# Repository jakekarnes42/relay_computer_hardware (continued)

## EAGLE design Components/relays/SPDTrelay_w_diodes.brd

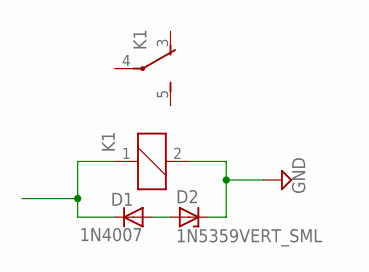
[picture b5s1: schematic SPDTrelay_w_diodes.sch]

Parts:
D1: 1N4007; RAD2,5
D2: 1N5359VERT_SML; RAD2.5_D2
K1: HF41F-12-Z

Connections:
D$1: D1.A, D2.A
GND: D2.C, K1.2
IN: D1.C, K1.1

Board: 2 copper layers, 3 parts (0 on the bottom side), 3 nets, no tracks yet.

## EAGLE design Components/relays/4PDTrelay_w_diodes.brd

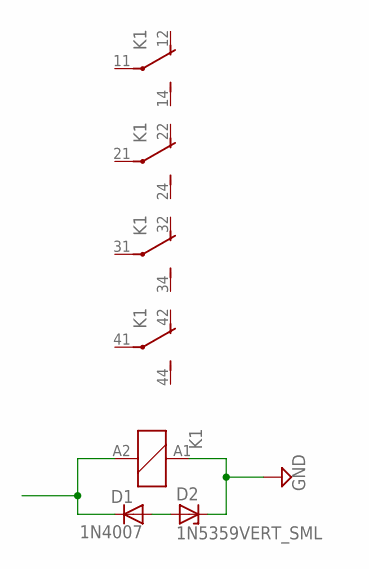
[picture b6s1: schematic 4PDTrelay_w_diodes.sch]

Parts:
D1: 1N4007; RAD2,5
D2: 1N5359VERT_SML; RAD2.5_D2
K1: PY14-02

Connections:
D$1: D1.A, D2.A
GND: D2.C, K1.A1 (1)
IN: D1.C, K1.A2 (2)

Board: 2 copper layers, 3 parts (0 on the bottom side), 3 nets, no tracks yet.

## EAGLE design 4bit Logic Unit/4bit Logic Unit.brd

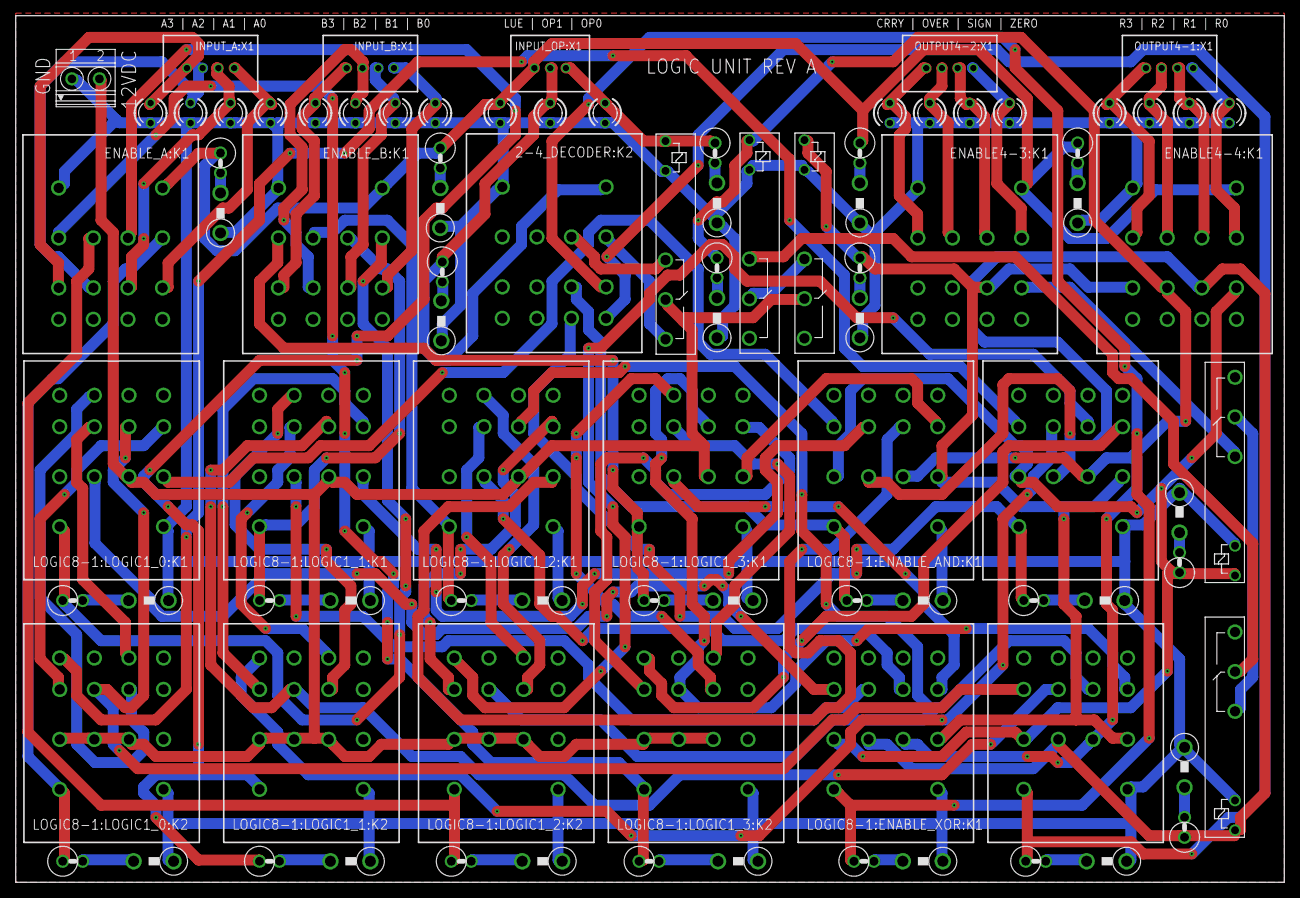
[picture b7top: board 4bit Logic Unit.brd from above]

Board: 2 copper layers, 161.3 x 110.2 mm, 91 parts (0 on the bottom side), 93 nets.

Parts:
2-4_DECODER:D1, 2-4_DECODER:D3: 1N4007; RAD2,5
2-4_DECODER:D2, 2-4_DECODER:D4: 1N5359; C1702-05
2-4_DECODER:K1: HF41F-12-Z
2-4_DECODER:K2: PY14-02
ENABLE4-3:D1, ENABLE4-4:D1: 1N4007; RAD2,5
ENABLE4-3:D2, ENABLE4-4:D2: 1N5359; C1702-05
ENABLE4-3:K1, ENABLE4-4:K1: PY14-02
ENABLE_A:D1: 1N4007; RAD2,5
ENABLE_A:D2: 1N5359; C1702-05
ENABLE_A:K1: PY14-02
ENABLE_B:D1: 1N4007; RAD2,5
ENABLE_B:D2: 1N5359; C1702-05
ENABLE_B:K1: PY14-02
INPUT_A:LED0, INPUT_A:LED1, INPUT_A:LED2, INPUT_A:LED3: LED3MM
INPUT_A:X1: 55932-0430
INPUT_B:LED0, INPUT_B:LED1, INPUT_B:LED2, INPUT_B:LED3: LED3MM
INPUT_B:X1: 55932-0430
INPUT_OP:LED0, INPUT_OP:LED1, INPUT_OP:LED2: LED3MM
INPUT_OP:X1: 55932-0330
LOGIC8-1:ENABLE_AND:D1, LOGIC8-1:ENABLE_NOT:D1, LOGIC8-1:ENABLE_OR:D1, LOGIC8-1:ENABLE_XOR:D1, LOGIC8-1:LOGIC1_0:D1, LOGIC8-1:LOGIC1_0:D3, LOGIC8-1:LOGIC1_1:D1, LOGIC8-1:LOGIC1_1:D3, LOGIC8-1:LOGIC1_2:D1, LOGIC8-1:LOGIC1_2:D3, LOGIC8-1:LOGIC1_3:D1, LOGIC8-1:LOGIC1_3:D3: 1N4007; RAD2,5
LOGIC8-1:ENABLE_AND:D2, LOGIC8-1:ENABLE_NOT:D2, LOGIC8-1:ENABLE_OR:D2, LOGIC8-1:ENABLE_XOR:D2, LOGIC8-1:LOGIC1_0:D2, LOGIC8-1:LOGIC1_0:D4, LOGIC8-1:LOGIC1_1:D2, LOGIC8-1:LOGIC1_1:D4, LOGIC8-1:LOGIC1_2:D2, LOGIC8-1:LOGIC1_2:D4, LOGIC8-1:LOGIC1_3:D2, LOGIC8-1:LOGIC1_3:D4: 1N5359; C1702-05
LOGIC8-1:ENABLE_AND:K1, LOGIC8-1:ENABLE_NOT:K1, LOGIC8-1:ENABLE_OR:K1, LOGIC8-1:ENABLE_XOR:K1, LOGIC8-1:LOGIC1_0:K1, LOGIC8-1:LOGIC1_0:K2, LOGIC8-1:LOGIC1_1:K1, LOGIC8-1:LOGIC1_1:K2, LOGIC8-1:LOGIC1_2:K1, LOGIC8-1:LOGIC1_2:K2, LOGIC8-1:LOGIC1_3:K1, LOGIC8-1:LOGIC1_3:K2: PY14-02
OUTPUT4-1:LED0, OUTPUT4-1:LED1, OUTPUT4-1:LED2, OUTPUT4-1:LED3, OUTPUT4-2:LED0, OUTPUT4-2:LED1, OUTPUT4-2:LED2, OUTPUT4-2:LED3: LED3MM
OUTPUT4-1:X1, OUTPUT4-2:X1: 55932-0430
PWR_BLK:PWR: PWR_BLK; 1751248
ZERO_DETECT1:D1, ZERO_DETECT1:D3, ZERO_DETECT1:D5, ZERO_DETECT1:D7: 1N4007; RAD2,5
ZERO_DETECT1:D2, ZERO_DETECT1:D4, ZERO_DETECT1:D6, ZERO_DETECT1:D8: 1N5359; C1702-05
ZERO_DETECT1:K1, ZERO_DETECT1:K2, ZERO_DETECT1:K3, ZERO_DETECT1:K4: HF41F-12-Z

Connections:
2-4_DECODER:D$1: 2-4_DECODER:D1.A, 2-4_DECODER:D2.A
2-4_DECODER:D$2: 2-4_DECODER:D3.A, 2-4_DECODER:D4.A
2-4_DECODER:N$1: 2-4_DECODER:K1.5, 2-4_DECODER:K2.41
2-4_DECODER:N$2: 2-4_DECODER:K1.3, 2-4_DECODER:K2.31
+12V: 2-4_DECODER:K1.4, LOGIC8-1:LOGIC1_0:K1.21, LOGIC8-1:LOGIC1_0:K2.21, LOGIC8-1:LOGIC1_0:K2.31, LOGIC8-1:LOGIC1_0:K2.41, LOGIC8-1:LOGIC1_1:K1.21, LOGIC8-1:LOGIC1_1:K2.21, LOGIC8-1:LOGIC1_1:K2.31, LOGIC8-1:LOGIC1_1:K2.41, LOGIC8-1:LOGIC1_2:K1.21, LOGIC8-1:LOGIC1_2:K2.21, LOGIC8-1:LOGIC1_2:K2.31, LOGIC8-1:LOGIC1_2:K2.41, LOGIC8-1:LOGIC1_3:K1.21, LOGIC8-1:LOGIC1_3:K2.21, LOGIC8-1:LOGIC1_3:K2.31, LOGIC8-1:LOGIC1_3:K2.41, PWR_BLK:PWR.2, ZERO_DETECT1:K1.4
CARRY: ENABLE4-3:K1.11, OUTPUT4-2:LED3.A, OUTPUT4-2:X1.1
ENABLE4-3:D$1: ENABLE4-3:D1.A, ENABLE4-3:D2.A
ENABLE4-4:D$1: ENABLE4-4:D1.A, ENABLE4-4:D2.A
ENABLE_A:D$1: ENABLE_A:D1.A, ENABLE_A:D2.A
ENABLE_B:D$1: ENABLE_B:D1.A, ENABLE_B:D2.A
GND: 2-4_DECODER:D2.C, 2-4_DECODER:D4.C, 2-4_DECODER:K1.2, 2-4_DECODER:K2.A1, ENABLE4-3:D2.C, ENABLE4-3:K1.A1, ENABLE4-4:D2.C, ENABLE4-4:K1.A1, ENABLE_A:D2.C, ENABLE_A:K1.A1, ENABLE_B:D2.C, ENABLE_B:K1.A1, INPUT_A:LED0.K, INPUT_A:LED1.K, INPUT_A:LED2.K, INPUT_A:LED3.K, INPUT_B:LED0.K, INPUT_B:LED1.K, INPUT_B:LED2.K, INPUT_B:LED3.K, INPUT_OP:LED0.K, INPUT_OP:LED1.K, INPUT_OP:LED2.K, LOGIC8-1:ENABLE_AND:D2.C, LOGIC8-1:ENABLE_AND:K1.A1, LOGIC8-1:ENABLE_NOT:D2.C, LOGIC8-1:ENABLE_NOT:K1.A1, LOGIC8-1:ENABLE_OR:D2.C, LOGIC8-1:ENABLE_OR:K1.A1, LOGIC8-1:ENABLE_XOR:D2.C, LOGIC8-1:ENABLE_XOR:K1.A1, LOGIC8-1:LOGIC1_0:D2.C, LOGIC8-1:LOGIC1_0:D4.C, LOGIC8-1:LOGIC1_0:K1.A1, LOGIC8-1:LOGIC1_0:K2.A1, LOGIC8-1:LOGIC1_1:D2.C, LOGIC8-1:LOGIC1_1:D4.C, LOGIC8-1:LOGIC1_1:K1.A1, LOGIC8-1:LOGIC1_1:K2.A1, LOGIC8-1:LOGIC1_2:D2.C, LOGIC8-1:LOGIC1_2:D4.C, LOGIC8-1:LOGIC1_2:K1.A1, LOGIC8-1:LOGIC1_2:K2.A1, LOGIC8-1:LOGIC1_3:D2.C, LOGIC8-1:LOGIC1_3:D4.C, LOGIC8-1:LOGIC1_3:K1.A1, LOGIC8-1:LOGIC1_3:K2.A1, OUTPUT4-1:LED0.K, OUTPUT4-1:LED1.K, OUTPUT4-1:LED2.K, OUTPUT4-1:LED3.K, OUTPUT4-2:LED0.K, OUTPUT4-2:LED1.K, OUTPUT4-2:LED2.K, OUTPUT4-2:LED3.K, PWR_BLK:PWR.1, ZERO_DETECT1:D2.C, ZERO_DETECT1:D4.C, ZERO_DETECT1:D6.C, ZERO_DETECT1:D8.C, ZERO_DETECT1:K1.2, ZERO_DETECT1:K2.2, ZERO_DETECT1:K3.2, ZERO_DETECT1:K4.2
LOGIC8-1:AND0: LOGIC8-1:ENABLE_AND:K1.44, LOGIC8-1:LOGIC1_0:K1.11
LOGIC8-1:AND1: LOGIC8-1:ENABLE_AND:K1.34, LOGIC8-1:LOGIC1_1:K1.11
LOGIC8-1:AND2: LOGIC8-1:ENABLE_AND:K1.24, LOGIC8-1:LOGIC1_2:K1.11
LOGIC8-1:AND3: LOGIC8-1:ENABLE_AND:K1.14, LOGIC8-1:LOGIC1_3:K1.11
LOGIC8-1:ENABLE_AND:D$1: LOGIC8-1:ENABLE_AND:D1.A, LOGIC8-1:ENABLE_AND:D2.A
LOGIC8-1:ENABLE_NOT:D$1: LOGIC8-1:ENABLE_NOT:D1.A, LOGIC8-1:ENABLE_NOT:D2.A
LOGIC8-1:ENABLE_OR:D$1: LOGIC8-1:ENABLE_OR:D1.A, LOGIC8-1:ENABLE_OR:D2.A
LOGIC8-1:ENABLE_XOR:D$1: LOGIC8-1:ENABLE_XOR:D1.A, LOGIC8-1:ENABLE_XOR:D2.A
LOGIC8-1:LOGIC1_0:D$1: LOGIC8-1:LOGIC1_0:D1.A, LOGIC8-1:LOGIC1_0:D2.A
LOGIC8-1:LOGIC1_0:D$2: LOGIC8-1:LOGIC1_0:D3.A, LOGIC8-1:LOGIC1_0:D4.A
LOGIC8-1:LOGIC1_0:N$1: LOGIC8-1:LOGIC1_0:K1.14, LOGIC8-1:LOGIC1_0:K2.44
LOGIC8-1:LOGIC1_0:N$3: LOGIC8-1:LOGIC1_0:K1.32, LOGIC8-1:LOGIC1_0:K2.24
LOGIC8-1:LOGIC1_0:N$4: LOGIC8-1:LOGIC1_0:K1.34, LOGIC8-1:LOGIC1_0:K2.22
LOGIC8-1:LOGIC1_1:D$1: LOGIC8-1:LOGIC1_1:D1.A, LOGIC8-1:LOGIC1_1:D2.A
LOGIC8-1:LOGIC1_1:D$2: LOGIC8-1:LOGIC1_1:D3.A, LOGIC8-1:LOGIC1_1:D4.A
LOGIC8-1:LOGIC1_1:N$1: LOGIC8-1:LOGIC1_1:K1.14, LOGIC8-1:LOGIC1_1:K2.44
LOGIC8-1:LOGIC1_1:N$3: LOGIC8-1:LOGIC1_1:K1.32, LOGIC8-1:LOGIC1_1:K2.24
LOGIC8-1:LOGIC1_1:N$4: LOGIC8-1:LOGIC1_1:K1.34, LOGIC8-1:LOGIC1_1:K2.22
LOGIC8-1:LOGIC1_2:D$1: LOGIC8-1:LOGIC1_2:D1.A, LOGIC8-1:LOGIC1_2:D2.A
LOGIC8-1:LOGIC1_2:D$2: LOGIC8-1:LOGIC1_2:D3.A, LOGIC8-1:LOGIC1_2:D4.A
LOGIC8-1:LOGIC1_2:N$1: LOGIC8-1:LOGIC1_2:K1.14, LOGIC8-1:LOGIC1_2:K2.44
LOGIC8-1:LOGIC1_2:N$3: LOGIC8-1:LOGIC1_2:K1.32, LOGIC8-1:LOGIC1_2:K2.24
LOGIC8-1:LOGIC1_2:N$4: LOGIC8-1:LOGIC1_2:K1.34, LOGIC8-1:LOGIC1_2:K2.22
LOGIC8-1:LOGIC1_3:D$1: LOGIC8-1:LOGIC1_3:D1.A, LOGIC8-1:LOGIC1_3:D2.A
LOGIC8-1:LOGIC1_3:D$2: LOGIC8-1:LOGIC1_3:D3.A, LOGIC8-1:LOGIC1_3:D4.A
LOGIC8-1:LOGIC1_3:N$1: LOGIC8-1:LOGIC1_3:K1.14, LOGIC8-1:LOGIC1_3:K2.44
LOGIC8-1:LOGIC1_3:N$3: LOGIC8-1:LOGIC1_3:K1.32, LOGIC8-1:LOGIC1_3:K2.24
LOGIC8-1:LOGIC1_3:N$4: LOGIC8-1:LOGIC1_3:K1.34, LOGIC8-1:LOGIC1_3:K2.22
LOGIC8-1:NOT0: LOGIC8-1:ENABLE_NOT:K1.44, LOGIC8-1:LOGIC1_0:K2.42
LOGIC8-1:NOT1: LOGIC8-1:ENABLE_NOT:K1.34, LOGIC8-1:LOGIC1_1:K2.42
LOGIC8-1:NOT2: LOGIC8-1:ENABLE_NOT:K1.24, LOGIC8-1:LOGIC1_2:K2.42
LOGIC8-1:NOT3: LOGIC8-1:ENABLE_NOT:K1.14, LOGIC8-1:LOGIC1_3:K2.42
LOGIC8-1:OR0: LOGIC8-1:ENABLE_OR:K1.44, LOGIC8-1:LOGIC1_0:K1.24, LOGIC8-1:LOGIC1_0:K2.34
LOGIC8-1:OR1: LOGIC8-1:ENABLE_OR:K1.34, LOGIC8-1:LOGIC1_1:K1.24, LOGIC8-1:LOGIC1_1:K2.34
LOGIC8-1:OR2: LOGIC8-1:ENABLE_OR:K1.24, LOGIC8-1:LOGIC1_2:K1.24, LOGIC8-1:LOGIC1_2:K2.34
LOGIC8-1:OR3: LOGIC8-1:ENABLE_OR:K1.14, LOGIC8-1:LOGIC1_3:K1.24, LOGIC8-1:LOGIC1_3:K2.34
LOGIC8-1:XOR0: LOGIC8-1:ENABLE_XOR:K1.44, LOGIC8-1:LOGIC1_0:K1.31
LOGIC8-1:XOR1: LOGIC8-1:ENABLE_XOR:K1.34, LOGIC8-1:LOGIC1_1:K1.31
LOGIC8-1:XOR2: LOGIC8-1:ENABLE_XOR:K1.24, LOGIC8-1:LOGIC1_2:K1.31
LOGIC8-1:XOR3: LOGIC8-1:ENABLE_XOR:K1.14, LOGIC8-1:LOGIC1_3:K1.31
LUE: ENABLE4-3:D1.C, ENABLE4-3:K1.A2, ENABLE4-4:D1.C, ENABLE4-4:K1.A2, ENABLE_A:D1.C, ENABLE_A:K1.A2, ENABLE_B:D1.C, ENABLE_B:K1.A2, INPUT_OP:LED2.A, INPUT_OP:X1.1
unnamed: ENABLE_A:K1.44, INPUT_A:LED0.A, INPUT_A:X1.4
unnamed: ENABLE_A:K1.34, INPUT_A:LED1.A, INPUT_A:X1.3
unnamed: ENABLE_A:K1.24, INPUT_A:LED2.A, INPUT_A:X1.2
unnamed: ENABLE_A:K1.14, INPUT_A:LED3.A, INPUT_A:X1.1
unnamed: ENABLE_B:K1.44, INPUT_B:LED0.A, INPUT_B:X1.4
unnamed: ENABLE_B:K1.34, INPUT_B:LED1.A, INPUT_B:X1.3
unnamed: ENABLE_B:K1.24, INPUT_B:LED2.A, INPUT_B:X1.2
unnamed: ENABLE_B:K1.14, INPUT_B:LED3.A, INPUT_B:X1.1
unnamed: ENABLE_B:K1.11, LOGIC8-1:LOGIC1_3:D1.C, LOGIC8-1:LOGIC1_3:K1.A2
unnamed: ENABLE_B:K1.21, LOGIC8-1:LOGIC1_2:D1.C, LOGIC8-1:LOGIC1_2:K1.A2
unnamed: ENABLE_B:K1.31, LOGIC8-1:LOGIC1_1:D1.C, LOGIC8-1:LOGIC1_1:K1.A2
unnamed: ENABLE_B:K1.41, LOGIC8-1:LOGIC1_0:D1.C, LOGIC8-1:LOGIC1_0:K1.A2
unnamed: 2-4_DECODER:D1.C, 2-4_DECODER:K1.1, INPUT_OP:LED0.A, INPUT_OP:X1.3
unnamed: ENABLE_A:K1.11, LOGIC8-1:LOGIC1_3:D3.C, LOGIC8-1:LOGIC1_3:K2.A2
unnamed: ENABLE_A:K1.21, LOGIC8-1:LOGIC1_2:D3.C, LOGIC8-1:LOGIC1_2:K2.A2
unnamed: ENABLE_A:K1.31, LOGIC8-1:LOGIC1_1:D3.C, LOGIC8-1:LOGIC1_1:K2.A2
unnamed: ENABLE_A:K1.41, LOGIC8-1:LOGIC1_0:D3.C, LOGIC8-1:LOGIC1_0:K2.A2
unnamed: 2-4_DECODER:D3.C, 2-4_DECODER:K2.A2, INPUT_OP:LED1.A, INPUT_OP:X1.2
unnamed: 2-4_DECODER:K2.44, LOGIC8-1:ENABLE_NOT:D1.C, LOGIC8-1:ENABLE_NOT:K1.A2
unnamed: 2-4_DECODER:K2.34, LOGIC8-1:ENABLE_AND:D1.C, LOGIC8-1:ENABLE_AND:K1.A2
unnamed: 2-4_DECODER:K2.42, LOGIC8-1:ENABLE_OR:D1.C, LOGIC8-1:ENABLE_OR:K1.A2
unnamed: 2-4_DECODER:K2.32, LOGIC8-1:ENABLE_XOR:D1.C, LOGIC8-1:ENABLE_XOR:K1.A2
unnamed: ENABLE4-3:K1.44, ZERO_DETECT1:K4.3
unnamed: ENABLE4-4:K1.44, LOGIC8-1:ENABLE_AND:K1.41, LOGIC8-1:ENABLE_NOT:K1.41, LOGIC8-1:ENABLE_OR:K1.41, LOGIC8-1:ENABLE_XOR:K1.41, ZERO_DETECT1:D7.C, ZERO_DETECT1:K4.1
unnamed: ENABLE4-4:K1.34, LOGIC8-1:ENABLE_AND:K1.31, LOGIC8-1:ENABLE_NOT:K1.31, LOGIC8-1:ENABLE_OR:K1.31, LOGIC8-1:ENABLE_XOR:K1.31, ZERO_DETECT1:D5.C, ZERO_DETECT1:K3.1
unnamed: ENABLE4-4:K1.24, LOGIC8-1:ENABLE_AND:K1.21, LOGIC8-1:ENABLE_NOT:K1.21, LOGIC8-1:ENABLE_OR:K1.21, LOGIC8-1:ENABLE_XOR:K1.21, ZERO_DETECT1:D3.C, ZERO_DETECT1:K2.1
unnamed: ENABLE4-3:K1.34, ENABLE4-4:K1.14, LOGIC8-1:ENABLE_AND:K1.11, LOGIC8-1:ENABLE_NOT:K1.11, LOGIC8-1:ENABLE_OR:K1.11, LOGIC8-1:ENABLE_XOR:K1.11, ZERO_DETECT1:D1.C, ZERO_DETECT1:K1.1
OVERFLOW: ENABLE4-3:K1.21, OUTPUT4-2:LED2.A, OUTPUT4-2:X1.2
R0: ENABLE4-4:K1.41, OUTPUT4-1:LED0.A, OUTPUT4-1:X1.4
R1: ENABLE4-4:K1.31, OUTPUT4-1:LED1.A, OUTPUT4-1:X1.3
R2: ENABLE4-4:K1.21, OUTPUT4-1:LED2.A, OUTPUT4-1:X1.2
R3: ENABLE4-4:K1.11, OUTPUT4-1:LED3.A, OUTPUT4-1:X1.1
SIGN: ENABLE4-3:K1.31, OUTPUT4-2:LED1.A, OUTPUT4-2:X1.3
ZERO: ENABLE4-3:K1.41, OUTPUT4-2:LED0.A, OUTPUT4-2:X1.4
ZERO_DETECT1:D$1: ZERO_DETECT1:D1.A, ZERO_DETECT1:D2.A
ZERO_DETECT1:D$2: ZERO_DETECT1:D3.A, ZERO_DETECT1:D4.A
ZERO_DETECT1:D$3: ZERO_DETECT1:D5.A, ZERO_DETECT1:D6.A
ZERO_DETECT1:D$4: ZERO_DETECT1:D7.A, ZERO_DETECT1:D8.A
ZERO_DETECT1:N$2: ZERO_DETECT1:K1.3, ZERO_DETECT1:K2.4
ZERO_DETECT1:N$3: ZERO_DETECT1:K2.3, ZERO_DETECT1:K3.4
ZERO_DETECT1:N$4: ZERO_DETECT1:K3.3, ZERO_DETECT1:K4.4

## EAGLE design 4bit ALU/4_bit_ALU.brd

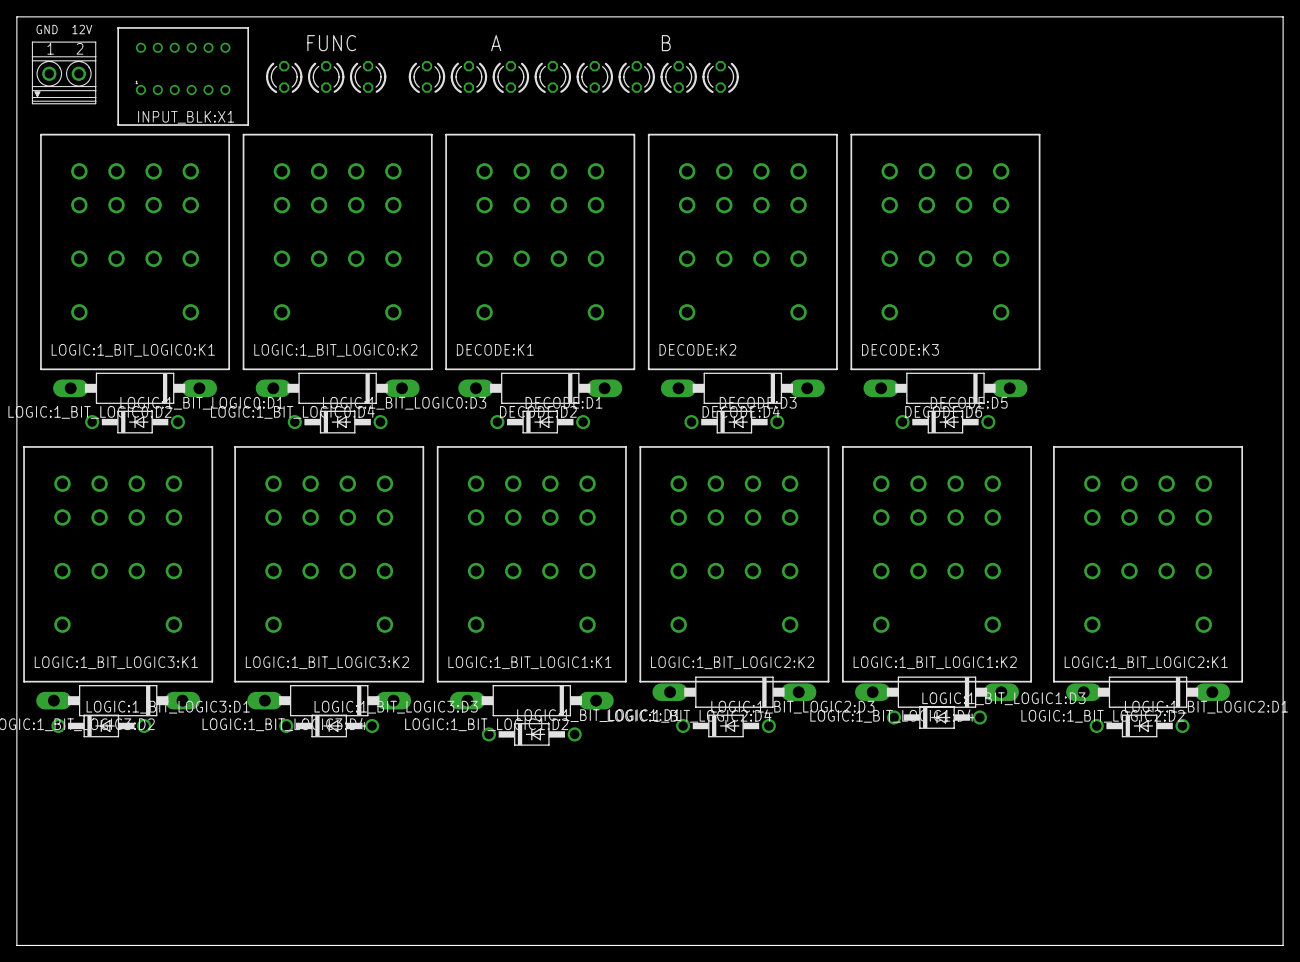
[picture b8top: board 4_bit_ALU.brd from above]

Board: 2 copper layers, 150.0 x 110.0 mm, 46 parts (0 on the bottom side), 46 nets, no tracks yet.

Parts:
DECODE:D1, DECODE:D3, DECODE:D5: 1N4007; DO41-10
DECODE:D2, DECODE:D4, DECODE:D6: 1N5359; C1702-15
DECODE:K1, DECODE:K2, DECODE:K3: PY14-02
INPUT_BLK:LED1, INPUT_BLK:LED2, INPUT_BLK:LED3, INPUT_BLK:LED4, INPUT_BLK:LED5, INPUT_BLK:LED6, INPUT_BLK:LED7, INPUT_BLK:LED8, INPUT_BLK:LED9, INPUT_BLK:LED10, INPUT_BLK:LED11: LED3MM
INPUT_BLK:X1: 55917-1230
LOGIC:1_BIT_LOGIC0:D1, LOGIC:1_BIT_LOGIC0:D3, LOGIC:1_BIT_LOGIC1:D1, LOGIC:1_BIT_LOGIC1:D3, LOGIC:1_BIT_LOGIC2:D1, LOGIC:1_BIT_LOGIC2:D3, LOGIC:1_BIT_LOGIC3:D1, LOGIC:1_BIT_LOGIC3:D3: 1N4007; DO41-10
LOGIC:1_BIT_LOGIC0:D2, LOGIC:1_BIT_LOGIC0:D4, LOGIC:1_BIT_LOGIC1:D2, LOGIC:1_BIT_LOGIC1:D4, LOGIC:1_BIT_LOGIC2:D2, LOGIC:1_BIT_LOGIC2:D4, LOGIC:1_BIT_LOGIC3:D2, LOGIC:1_BIT_LOGIC3:D4: 1N5359; C1702-15
LOGIC:1_BIT_LOGIC0:K1, LOGIC:1_BIT_LOGIC0:K2, LOGIC:1_BIT_LOGIC1:K1, LOGIC:1_BIT_LOGIC1:K2, LOGIC:1_BIT_LOGIC2:K1, LOGIC:1_BIT_LOGIC2:K2, LOGIC:1_BIT_LOGIC3:K1, LOGIC:1_BIT_LOGIC3:K2: PY14-02
PWR_BLK:PWR: PWR_BLK; 1751248

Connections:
+12V: DECODE:K1.41, LOGIC:1_BIT_LOGIC0:K1.21, LOGIC:1_BIT_LOGIC0:K1.31, LOGIC:1_BIT_LOGIC0:K1.41, LOGIC:1_BIT_LOGIC0:K2.21, LOGIC:1_BIT_LOGIC1:K1.21, LOGIC:1_BIT_LOGIC1:K1.31, LOGIC:1_BIT_LOGIC1:K1.41, LOGIC:1_BIT_LOGIC1:K2.21, LOGIC:1_BIT_LOGIC2:K1.21, LOGIC:1_BIT_LOGIC2:K1.31, LOGIC:1_BIT_LOGIC2:K1.41, LOGIC:1_BIT_LOGIC2:K2.21, LOGIC:1_BIT_LOGIC3:K1.21, LOGIC:1_BIT_LOGIC3:K1.31, LOGIC:1_BIT_LOGIC3:K1.41, LOGIC:1_BIT_LOGIC3:K2.21, PWR_BLK:PWR.2
A0: INPUT_BLK:LED7.A, INPUT_BLK:X1.11, LOGIC:1_BIT_LOGIC0:D1.C, LOGIC:1_BIT_LOGIC0:K1.A2
A1: INPUT_BLK:LED6.A, INPUT_BLK:X1.9, LOGIC:1_BIT_LOGIC1:D1.C, LOGIC:1_BIT_LOGIC1:K1.A2
A2: INPUT_BLK:LED5.A, INPUT_BLK:X1.7, LOGIC:1_BIT_LOGIC2:D1.C, LOGIC:1_BIT_LOGIC2:K1.A2
A3: INPUT_BLK:LED4.A, INPUT_BLK:X1.5, LOGIC:1_BIT_LOGIC3:D1.C, LOGIC:1_BIT_LOGIC3:K1.A2
B0: INPUT_BLK:LED11.A, INPUT_BLK:X1.6, LOGIC:1_BIT_LOGIC0:D3.C, LOGIC:1_BIT_LOGIC0:K2.A2
B1: INPUT_BLK:LED10.A, INPUT_BLK:X1.8, LOGIC:1_BIT_LOGIC1:D3.C, LOGIC:1_BIT_LOGIC1:K2.A2
B2: INPUT_BLK:LED9.A, INPUT_BLK:X1.10, LOGIC:1_BIT_LOGIC2:D3.C, LOGIC:1_BIT_LOGIC2:K2.A2
B3: INPUT_BLK:LED8.A, INPUT_BLK:X1.12, LOGIC:1_BIT_LOGIC3:D3.C, LOGIC:1_BIT_LOGIC3:K2.A2
DECODE:D$1: DECODE:D1.A, DECODE:D2.A
DECODE:D$2: DECODE:D3.A, DECODE:D4.A
DECODE:D$3: DECODE:D5.A, DECODE:D6.A
DECODE:N$1: DECODE:K1.44, DECODE:K2.41
DECODE:N$2: DECODE:K1.42, DECODE:K2.31
DECODE:N$3: DECODE:K2.44, DECODE:K3.41
DECODE:N$4: DECODE:K2.42, DECODE:K3.31
DECODE:N$5: DECODE:K2.34, DECODE:K3.21
DECODE:N$6: DECODE:K2.32, DECODE:K3.11
FUNC0: DECODE:D5.C, DECODE:K3.A2, INPUT_BLK:LED3.A, INPUT_BLK:X1.3
FUNC1: DECODE:D3.C, DECODE:K2.A2, INPUT_BLK:LED2.A, INPUT_BLK:X1.1
FUNC2: DECODE:D1.C, DECODE:K1.A2, INPUT_BLK:LED1.A, INPUT_BLK:X1.2
GND: DECODE:D2.C, DECODE:D4.C, DECODE:D6.C, DECODE:K1.A1, DECODE:K2.A1, DECODE:K3.A1, INPUT_BLK:LED1.K, INPUT_BLK:LED2.K, INPUT_BLK:LED3.K, INPUT_BLK:LED4.K, INPUT_BLK:LED5.K, INPUT_BLK:LED6.K, INPUT_BLK:LED7.K, INPUT_BLK:LED8.K, INPUT_BLK:LED9.K, INPUT_BLK:LED10.K, INPUT_BLK:LED11.K, LOGIC:1_BIT_LOGIC0:D2.C, LOGIC:1_BIT_LOGIC0:D4.C, LOGIC:1_BIT_LOGIC0:K1.A1, LOGIC:1_BIT_LOGIC0:K2.A1, LOGIC:1_BIT_LOGIC1:D2.C, LOGIC:1_BIT_LOGIC1:D4.C, LOGIC:1_BIT_LOGIC1:K1.A1, LOGIC:1_BIT_LOGIC1:K2.A1, LOGIC:1_BIT_LOGIC2:D2.C, LOGIC:1_BIT_LOGIC2:D4.C, LOGIC:1_BIT_LOGIC2:K1.A1, LOGIC:1_BIT_LOGIC2:K2.A1, LOGIC:1_BIT_LOGIC3:D2.C, LOGIC:1_BIT_LOGIC3:D4.C, LOGIC:1_BIT_LOGIC3:K1.A1, LOGIC:1_BIT_LOGIC3:K2.A1, PWR_BLK:PWR.1
LOGIC:1_BIT_LOGIC0:D$1: LOGIC:1_BIT_LOGIC0:D1.A, LOGIC:1_BIT_LOGIC0:D2.A
LOGIC:1_BIT_LOGIC0:D$2: LOGIC:1_BIT_LOGIC0:D3.A, LOGIC:1_BIT_LOGIC0:D4.A
LOGIC:1_BIT_LOGIC0:N$1: LOGIC:1_BIT_LOGIC0:K1.44, LOGIC:1_BIT_LOGIC0:K2.14
LOGIC:1_BIT_LOGIC0:N$2: LOGIC:1_BIT_LOGIC0:K1.24, LOGIC:1_BIT_LOGIC0:K2.32
LOGIC:1_BIT_LOGIC0:N$3: LOGIC:1_BIT_LOGIC0:K1.22, LOGIC:1_BIT_LOGIC0:K2.34
LOGIC:1_BIT_LOGIC1:D$1: LOGIC:1_BIT_LOGIC1:D1.A, LOGIC:1_BIT_LOGIC1:D2.A
LOGIC:1_BIT_LOGIC1:D$2: LOGIC:1_BIT_LOGIC1:D3.A, LOGIC:1_BIT_LOGIC1:D4.A
LOGIC:1_BIT_LOGIC1:N$1: LOGIC:1_BIT_LOGIC1:K1.44, LOGIC:1_BIT_LOGIC1:K2.14
LOGIC:1_BIT_LOGIC1:N$2: LOGIC:1_BIT_LOGIC1:K1.24, LOGIC:1_BIT_LOGIC1:K2.32
LOGIC:1_BIT_LOGIC1:N$3: LOGIC:1_BIT_LOGIC1:K1.22, LOGIC:1_BIT_LOGIC1:K2.34
LOGIC:1_BIT_LOGIC2:D$1: LOGIC:1_BIT_LOGIC2:D1.A, LOGIC:1_BIT_LOGIC2:D2.A
LOGIC:1_BIT_LOGIC2:D$2: LOGIC:1_BIT_LOGIC2:D3.A, LOGIC:1_BIT_LOGIC2:D4.A
LOGIC:1_BIT_LOGIC2:N$1: LOGIC:1_BIT_LOGIC2:K1.44, LOGIC:1_BIT_LOGIC2:K2.14
LOGIC:1_BIT_LOGIC2:N$2: LOGIC:1_BIT_LOGIC2:K1.24, LOGIC:1_BIT_LOGIC2:K2.32
LOGIC:1_BIT_LOGIC2:N$3: LOGIC:1_BIT_LOGIC2:K1.22, LOGIC:1_BIT_LOGIC2:K2.34
LOGIC:1_BIT_LOGIC3:D$1: LOGIC:1_BIT_LOGIC3:D1.A, LOGIC:1_BIT_LOGIC3:D2.A
LOGIC:1_BIT_LOGIC3:D$2: LOGIC:1_BIT_LOGIC3:D3.A, LOGIC:1_BIT_LOGIC3:D4.A
LOGIC:1_BIT_LOGIC3:N$1: LOGIC:1_BIT_LOGIC3:K1.44, LOGIC:1_BIT_LOGIC3:K2.14
LOGIC:1_BIT_LOGIC3:N$2: LOGIC:1_BIT_LOGIC3:K1.24, LOGIC:1_BIT_LOGIC3:K2.32
LOGIC:1_BIT_LOGIC3:N$3: LOGIC:1_BIT_LOGIC3:K1.22, LOGIC:1_BIT_LOGIC3:K2.34
OR0: LOGIC:1_BIT_LOGIC0:K1.34, LOGIC:1_BIT_LOGIC0:K2.24
OR1: LOGIC:1_BIT_LOGIC1:K1.34, LOGIC:1_BIT_LOGIC1:K2.24
OR2: LOGIC:1_BIT_LOGIC2:K1.34, LOGIC:1_BIT_LOGIC2:K2.24
OR3: LOGIC:1_BIT_LOGIC3:K1.34, LOGIC:1_BIT_LOGIC3:K2.24

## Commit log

2017-06-07 Initial checkin
2017-06-08 Fixing GND terminal on relay
2017-06-08 Removing WIP adder
2017-06-08 Fixed wiring for 1 bit logic block
2017-06-08 Improving .gitignore with additional backup suffixes
2017-06-08 Removing bad board and updating with correct logic block
2017-06-08 Removing B and C LEDs since relays have indicator LEDs
2017-06-09 Adding DRU with OSH park compatibility and required thickness
2017-06-09 Adding 1 bit logic block rev B
2017-08-27 Adding Adafruit's BeagleBone cape template
2017-08-27 Adding custom parts library with parts used in project
2017-08-27 Quick start of 4bit ALU controller cape
2017-08-27 Pretty high level outline for ALU
2017-09-03 Adding HONGFA SPST and SPDT PCB-mount relays
2017-09-10 Added official BTS442E2 part to library from Infineon site
2017-09-10 Adding connectors and diodes to library
2017-09-10 Adding coil-suppressed relay as reusable component
2017-09-10 WIP: 4bit ALU. Input and 3-to-8 decoder
2017-09-11 Updating README.md
2017-10-01 Creating re-usable suppressed relay components w/ vertical diodes
2017-10-01 Adding 3 and 4 pin single-row connectors
2017-10-02 WIP: start 4-bit Arithmetic Unit
2017-10-03 Finishing 4bit AU
2017-10-03 WIP: starting 4bit AU board. TODO: text and overlap checking
2017-10-03 Finishing 4bit AU. Text is actually correct when it appears offset. Worth doing a logical double-check
2017-10-04 Finishing 4bit LU. Text is actually correct when it appears offset. Worth doing a logical double-check
2017-10-05 Prettier dual rail adder
2017-10-06 Adding new connector, making existing ones consistent
2017-10-06 Using updated connectors
2017-12-02 Adding register board (WIP)
2017-12-02 Part Library updates
2017-12-02 Defining input signals for LU
2017-12-02 Minor formatting changes
2018-01-28 Adding TMP registers back into Register Board
2018-01-29 Adding 4 pin female header
2018-01-29 Re-arranging pins for high-side power switch
2018-01-29 WIP: skeleton of BBB test board
2018-01-30 Renaming power switch pins for consistency
2018-01-30 Finishing BBB Connection Test Board Rev A
2018-03-13 Correcting footprint for SPST and SPDT relays
2018-03-13 Added MCP23017 to part library. Copied from adafruit
2018-03-13 Added 100UF cap to part library. Copied from sparkfun
2018-03-15 Adding 4.7k resistor. Shrinking 1N4007 diode footprint
2018-03-15 Shrinking 1N5359 diode footprint
2018-03-15 Added 0.1UF cap
2018-03-15 Updating components with latest library updates
2018-03-18 Adding static labels to small parts
2018-03-18 Ensuring components have most up-to-date part footprints
2018-03-18 WIP: Starting BBB Connection Test Board rev B. Added MCP23017
2018-03-18 WIP: starting layout of BBB conn. test board rev B
2018-03-19 Almost finished with Rev B of connector board. Comestic changes only
2018-03-19 Increasing size of library parts
2018-03-19 Adding pull down resistors for inputs to MCP23017
2018-03-19 Ensuring part names are in tName layer so they appear on silkscreen
2018-03-19 Finishing touches of BBB Connection test Rev B board. Awaiting final review
2018-03-21 Finalize BBB Connection Test Board Rev B. Sending this version to fab.
2018-06-06 The AU opcode wires were switched
2018-06-06 Fixing AU subtraction CARRY bug
2018-10-27 WIP: Starting 2bit register board for testing
2018-10-27 Compatibility updates (should be no functional changes)
2018-11-04 Completed 2bit Register Board Rev A. Sent to OSH Park
2018-12-30 Little extra spacing between holes for easier soldering of 1N5359
2018-12-30 Cleanup and removal of obsolete boards
2018-12-30 Update latest library and add capacitor to power block
2018-12-30 Remove unnecessary boards
